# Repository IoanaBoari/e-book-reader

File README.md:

### OpenBook - Project

## Block Diagram

---
## Bill Of Materials (BOM)
| Component                   | Source                                                                                                                                                                      | Datasheet                                               |
|-----------------------------|-----------------------------------------------------------------------------------------------------------------------------------------------------------------------------|---------------------------------------------------------|
| Button                      | [Mouser](https://ro.mouser.com/ProductDetail/CK/KMR221GULCLFS?qs=u2NJ%252B70r0goBXaNk7IrU0Q%3D%3D)                                                                          |[Datasheet](https://www.ckswitches.com/media/1479/kmr2.pdf)|
| Capacitor SUPERCAP          | [Mouser](https://ro.mouser.com/ProductDetail/Seiko-Semiconductors/CPH3225A?qs=3etwrb1wR%252BhUOph6lAO7eg%3D%3D)                                                             | [Datasheet](https://ro.mouser.com/datasheet/2/360/Seiko_Instruments_MicroBattery_E_20230330_2024Jan_-3561061.pdf)|
| Capacitor 100nF             | [Mouser](https://ro.mouser.com/ProductDetail/KEMET/C0402C104K4RAL?qs=pIZUS6sqCWCaMuP2QVR%2Fog%3D%3D)                                                                        | [Datasheet](https://ro.mouser.com/datasheet/2/447/KEM_C1018_X7R_SnPb_SMD-3316276.pdf)|
| Capacitor 4.7uF             | [Mouser](https://ro.mouser.com/ProductDetail/KEMET/C0402C475M9PAC7411?qs=cpo3%2FpBou2jRzZxyxJnMGg%3D%3D)                                                                    | [Datasheet](https://ro.mouser.com/datasheet/2/447/KEM_C1006_X5R_SMD-3316465.pdf)|
| Capacitor 100uF TANT        | [Mouser](https://ro.mouser.com/ProductDetail/KYOCERA-AVX/TAJW107M010RNJ?qs=Wtp%252Bf%2FAeVqIH8v1VxV%252B1Rg%3D%3D)                                                          | [Datasheet](https://ro.mouser.com/datasheet/2/40/TAJ-3165264.pdf)|
| Capacitor 4.7uF / 25V       | [Mouser](https://ro.mouser.com/ProductDetail/KYOCERA-AVX/12063C475KAZ2A?qs=%252BdQmOuGyFcG3LdbVp5waMw%3D%3D)                                                                | [Datasheet](https://ro.mouser.com/datasheet/2/40/X7RDielectric-2943470.pdf)|
| Capacitor 1uF               | [Mouser](https://ro.mouser.com/ProductDetail/KEMET/C0402C105K9PACTU?qs=UdQET6xYxVCMExqTDkuPeQ%3D%3D)                                                                        | [Datasheet](https://ro.mouser.com/datasheet/2/447/KEM_C1006_X5R_SMD-3316465.pdf)|
| Capacitor 10uF              | [Mouser](https://ro.mouser.com/ProductDetail/KEMET/C0402C106M9PACTU?qs=x4XeXhDQKnp%252Bz0lMlwMC3A%3D%3D)                                                                    | [Datasheet](https://ro.mouser.com/datasheet/2/447/KEM_C1006_X5R_SMD-3316465.pdf)|
| CHG_LED                     | [CPC](https://cpc.farnell.com/kingbright/kpg-1608zgc/led-smd-0603-grn/dp/SC20796)                                                                                           | [Datasheet](https://www.farnell.com/datasheets/2046349.pdf)|
| USBLC6-2SC6Y                | [Mouser](https://ro.mouser.com/ProductDetail/STMicroelectronics/USBLC6-2SC6Y?qs=gNDSiZmRJS%2FOgDexvXkdow%3D%3D)                                                             | [Datasheet](https://ro.mouser.com/datasheet/2/389/usblc6_2sc6y-1852505.pdf)|
| PGB1010603MR                | [Mouser](https://ro.mouser.com/ProductDetail/Littelfuse/PGB1010603MR?qs=gu7KAQ731URLg4GSnNNN7Q%3D%3D)                                                                       | [Datasheet](https://www.littelfuse.com/assetdocs/pulseguard-esd-suppressors-pgb1-datasheet?assetguid=8a337998-d54d-466b-be4e-dc5bcd1f9321)|
| SD0805S020S1R0              | [Mouser](https://ro.mouser.com/ProductDetail/KYOCERA-AVX/SD0805S020S1R0?qs=jCA%252BPfw4LHbpkAoSnwrdjw%3D%3D)                                                                | [Datasheet](https://ro.mouser.com/datasheet/2/40/schottky-3165252.pdf)|
| MBR0530                     | [Mouser](https://ro.mouser.com/ProductDetail/onsemi/MBR0530T3G?qs=3JMERSakebpEmdUS6GetdQ%3D%3D)                                                                             | [Datasheet](https://www.onsemi.com/products/discrete-power-modules/schottky-diodes-schottky-rectifiers/mbr0530t3g)|
| Solder Jumper               | [Grabcad](https://grabcad.com/library/solder-jumpers-1)                                                                                                                     | [Datasheet](https://grabcad.com/library/solder-jumpers-1)|
| Capacitor 1uF / 50V         | [Mouser](https://ro.mouser.com/ProductDetail/TDK/C1608X7R1H105K080AB?qs=sGAEpiMZZMsh%252B1woXyUXjwVqLNpRsvnQGmKhuYn4DWE%3D)                                                 | [Datasheet](https://product.tdk.com/system/files/dam/doc/product/capacitor/ceramic/mlcc/catalog/mlcc_commercial_general_en.pdf)|
| Capacitor 0.1uF / 50V       | [Farnell](https://ro.farnell.com/multicomp-pro/mcmlr50v104kx7r/ceramic-capacitor-0-1uf-50v-x7r/dp/1600875?srsltid=AfmBOop-NuqSwaWYAsNDvdMnjraBeqfj0sl8f99iLZ_KJc8xpnT4fSqT) | [Datasheet](https://www.farnell.com/datasheets/2873577.pdf?_gl=1*x28a2*_gcl_au*MTYwODAzNzc2OC4xNzQzNDM1MjM4)|
| BD5229G-TR                  | [Mouser](https://ro.mouser.com/ProductDetail/ROHM-Semiconductor/BD5229G-TR?qs=4kLU8WoGk0vvnhrrYwdszw%3D%3D)                                                                 | [Datasheet](https://fscdn.rohm.com/en/products/databook/datasheet/ic/power/voltage_detector/bd52xxg-e.pdf)|
| XC6220A331MR-G              | [Mouser](https://ro.mouser.com/ProductDetail/Torex-Semiconductor/XC6220A331MR-G?qs=AsjdqWjXhJ8ZSWznL1J0gg%3D%3D)                                                            | [Datasheet](https://ro.mouser.com/datasheet/2/760/xc6220-3371556.pdf)|
| FH34SRJ-24S-0.5SH_99_       | [Mouser](https://ro.mouser.com/ProductDetail/Hirose-Connector/FH34SRJ-24S-0.5SH99?qs=vcbW%252B4%252BSTIpKBl5ap9J8Fw%3D%3D)                                                  | [Datasheet](https://ro.mouser.com/datasheet/2/185/FH34SRJ_24S_0_5SH_99__CL0580_1255_6_99_2DDrawing_0-1615044.pdf)|
| SAMACSYS_PARTS_USB4110-GF-A | [Mouser](https://ro.mouser.com/ProductDetail/GCT/USB4110-GF-A?qs=KUoIvG%2F9IlYiZvIXQjyJeA%3D%3D)                                                                            | [Datasheet](https://ro.mouser.com/datasheet/2/837/GCT_USB4110_Product_Drawing___20k_cycles-3455479.pdf)|
| QWIIC_RIGHT_ANGLEA          | [Mouser](https://ro.mouser.com/ProductDetail/JST-Commercial/SM04B-SRSS-TBLFSN?qs=cdbOS8ANM9B3FdyA6cNU2A%3D%3D)                                                              | [Datasheet](https://ro.mouser.com/datasheet/2/564/eSR_SZ-3476820.pdf)|
| 112A-TAAR-R03_ATTEND        | [LCSC](https://www.lcsc.com/product-detail/SD-Card-Connectors_Attend-Technology-112A-TAAR-R03_C6970445.html)                                                                | [Datasheet](https://www.lcsc.com/datasheet/lcsc_datasheet_2411220717_Attend-Technology-112A-TAAR-R03_C6970445.pdf)|
| Bobina                      | [Mouser](https://ro.mouser.com/ProductDetail/Wurth-Elektronik/744043680?qs=PGXP4M47uW6VkZq%252BkzjrHA%3D%3D)                                                                | [Datasheet](https://www.we-online.com/components/products/datasheet/744043680.pdf)|
| MCP73831                    | [Mouser](https://ro.mouser.com/ProductDetail/Microchip-Technology/MCP73831-2ACI-MC?qs=hH%252BOa0VZEiBneYTVdpuVdg%3D%3D)                                                     | [Datasheet](https://ro.mouser.com/datasheet/2/268/MCP73831_Family_Data_Sheet_DS20001984H-3441711.pdf)|
| PFMF.050.1                  | [Mouser](https://ro.mouser.com/ProductDetail/Schurter/PFMF.050.2?qs=1auRipcfynCums5v1iucSA%3D%3D)                                                                           | [Datasheet](https://ro.mouser.com/datasheet/2/358/typ_PFMF-1275918.pdf)|
| DMG2305UX-7                 | [Mouser](https://ro.mouser.com/ProductDetail/Diodes-Incorporated/DMG2305UX-7?qs=L1DZKBg7t5F%2FNBHrjfxC%252Bg%3D%3D)                                                         | [Datasheet](https://www.diodes.com/assets/Datasheets/DMG2305UX.pdf)|
| SI1308EDL-T1-GE3            | [Mouser](https://ro.mouser.com/ProductDetail/Vishay-Semiconductors/SI1308EDL-T1-GE3?qs=bX1%252BNvsK%2FBramh9tgpOaEw%3D%3D)                                                  | [Datasheet](https://www.vishay.com/docs/63399/si1308edl.pdf)|
| Resistor 10K                | [DigiKey](https://www.digikey.com/en/products/detail/venkel/CR0402-10W-102JT/12332774)                                                                                      | [Datasheet](https://data.venkel.com/documents/cr-series?_gl=1*mn27ew*_ga*MTAzMTIxOTYyMS4xNzQzNzU5MjAy*_ga_JRKGBZNVM8*MTc0Mzc1OTIwMS4xLjAuMTc0Mzc1OTIwMi41OS4wLjA.)|
| Resistor 100K               | [Venkel](https://venkel.com/part/CR0402-16W-1003FT)                                                                                                                         | [Datasheet](https://data.venkel.com/documents/cr-series?_gl=1*oleae1*_ga*MTAzMTIxOTYyMS4xNzQzNzU5MjAy*_ga_JRKGBZNVM8*MTc0Mzc1OTIwMS4xLjEuMTc0Mzc1OTM0My4zNi4wLjA.)|
| Resistor 5k1                | [Venkel](https://venkel.com/part/CR0402-10W-5101FT)                                                                                                                         | [Datasheet](https://data.venkel.com/documents/cr-series?_gl=1*1e041jc*_ga*MTAzMTIxOTYyMS4xNzQzNzU5MjAy*_ga_JRKGBZNVM8*MTc0Mzc1OTIwMS4xLjEuMTc0Mzc1OTU2Ny41MS4wLjA.)|
| Resistor 2k                 | [Venkel](https://www.venkel.com/part/CR0402-16W-2002FT)                                                                                                                     | [Datasheet](https://data.venkel.com/documents/cr-series?_gl=1*1sqolfs*_ga*MTAzMTIxOTYyMS4xNzQzNzU5MjAy*_ga_JRKGBZNVM8*MTc0Mzc1OTIwMS4xLjEuMTc0Mzc1OTY2OS4zNC4wLjA.)|
| Resistor 0.47               | [Mouser](https://ro.mouser.com/ProductDetail/Vishay-Beyschlag/MCT06030C4700FP500?qs=XsZ9OvPb0dt82KlzjdcMjQ%3D%3D)                                                           | [Datasheet](https://www.vishay.com/docs/28705/mcx0x0xpro.pdf)|
| BME688                      | [Mouser](https://ro.mouser.com/ProductDetail/Bosch-Sensortec/BME688?qs=IS%252B4QmGtzzqQoVDscqwx3A%3D%3D)                                                                    | [Datasheet](https://ro.mouser.com/datasheet/2/783/bst_bme688_fl000-2307034.pdf)|
| W25Q512JVEIQ                | [Mouser](https://ro.mouser.com/ProductDetail/Winbond/W25Q512JVEIQ?qs=l7cgNqFNU1jw6svr3at6tA%3D%3D)                                                                          | [Datasheet](https://ro.mouser.com/datasheet/2/949/Winbond_W25Q512JV_Datasheet-3240039.pdf)|
| ESP32-C6-WROOM-1-N8         | [Mouser](https://ro.mouser.com/ProductDetail/Espressif-Systems/ESP32-C6-WROOM-1-N8?qs=8Wlm6%252BaMh8ST02Gmwp74cw%3D%3D)                                                     | [Datasheet](https://ro.mouser.com/datasheet/2/891/Espressif_ESP32_C6_WROOM_1__Datasheet_V0_1_PRELIMI-3239987.pdf)|
| DS3231SN#                   | [Mouser](https://ro.mouser.com/ProductDetail/Analog-Devices-Maxim-Integrated/DS3231SN?qs=1eQvB6Dk1vhUlr8%2FOrV0Fw%3D%3D)                                                    | [Datasheet](https://ro.mouser.com/datasheet/2/609/DS3231-3421123.pdf)|
| MAX17048G+T10               | [Mouser](https://ro.mouser.com/ProductDetail/Analog-Devices-Maxim-Integrated/MAX17048G%2bT10?qs=D7PJwyCwLAoGnnn8jEPRBQ%3D%3D)                                               | [Datasheet](https://ro.mouser.com/datasheet/2/609/MAX17048_MAX17049-3469099.pdf)|
| Test Pad                    | [DigiKey](https://www.digikey.com/en/products/detail/keystone-electronics/5006/255330)                                                                                      | [Datasheet](https://www.keyelco.com/userAssets/file/M65p56.pdf)|

---

# Hardware Functionality

**Power Supply & Energy Management:**
- **USB with ESD:** Provides power and protects data lines.
- **Li-Po Charging Circuit - MCP73831:** Controlled charging for the 1800 mAh battery.
- **Li-Po Battery & LDO Voltage Regulator:** Regulates voltage to 3.3V for all modules.

**Microcontroller & Interfaces:**
- **ESP32-C6:**
    - **SPI:** Connects NOR Flash memory, SD card, and e-paper display.
    - **I2C:** Connects RTC DS3231, BME688 sensor, and expansion modules.
    - **UART:** For debugging and serial communication.
    - **GPIO:** For buttons and test pads.

**Storage & Display Modules:**
- **NOR Flash Memory (SPI)** Fast storage for firmware and data.
- **SD Card (SPI)** Expands storage capacity.
- **E-Paper Display:** Low-power, precise updates, controlled via SPI.

**Additional Modules & Sensors:**
- **RTC DS3231 (I2C):** Real-time clock.
- **BME688 Sensor (I2C):** Measures temperature, humidity, pressure, and air quality.
- **Qwiic/Stemma QT Connector (I2C):** Allows expansion with additional modules.
- **Test Pads & Buttons (GPIO):** Facilitate direct control and diagnostics.

**Power Optimization:**
- **ESP32-C6 Low-Power Mode:** Reduces consumption through dynamic frequency and activity management.
- **Stable LDO:** Ensures a constant 3.3V voltage.
- **SMD Components (e.g., 0402 capacitors):** Minimize consumption through small size and improved efficiency.

---

# ESP32-C6 Pin Mapping

| Nume | GPIO        | Usage                                          | Notes                                                                                                                           |
|------|-------------|------------------------------------------------|---------------------------------------------------------------------------------------------------------------------------------|
| 3V3  | 3V3         | 3.3V Power Supply                               | Voltage source for ESP32-C6 and logic components.                                                                       |
| SCK (SPI) | IO6         | SPI Clock                               | Provides the clock signal for high-speed data transfers.                                                                           |
| MOSI (SPI) | IO7         | SPI Data Transmission                           | Sends data to NOR Flash, SD Card, and E-Paper.                                                                               |
| MISO (SPI) | IO2         | SPI Data Reception                            | Receives data from SPI devices.                                                                                          |
| FLASH_CS | IO11        | SPI Chip Select for NOR Flash                | Selects the NOR Flash memory on the SPI bus.                                                                                 |
| EPD_CS | IO10        | SPI Chip Select for E-Paper                   | Selects the e-paper display.                                                                                                    |
| SDA (I2C) | IO21        | I2C Data Line                              | Connects RTC DS3231, BME688 sensor, and Qwiic/Stemma QT connector.                                                           |
| SCL (I2C) | IO22        | I2C Clock Line                              | Synchronizes I2C communication.                                                                                                 |
| TX (UART) | TXD0/GPIO16 | UART Data Transmission                          | Used for debugging and serial communication.                                                                                   |
| RX (UART) | RXD0/GPIO17 | UART Data Reception                             | Used for debugging and serial communication.                                                                                   |
| Buton Reset | EN          | ESP32-C6 Reset                              | Pin dedicat pentru resetul sistemului.                                                                                          |
| Buton Boot | IO9         | Bootloader Entry                          | Dedicated pin to enter boot mode.                                                                                       |
| Buton Change | IO15        | Operation Mode Switch                          | Allows switching between different operating modes.                                                                               |
| EPD DC | IO5         | Data/Command for E-Paper                   | Distinguishes between command and data signals for the display.                                                                |
| EPD RST | IO23        | E-Paper Reset                               | Resets the e-paper display when needed.                                                                                   |
| EPD BUSY | IO3         | E-Paper Busy Indicator                        | Signal indicating if the display is currently busy.                                                                                   |
| INT_RTC | IO0         | RTC Interrupt Signal (DS3231)        | Triggers the microcontroller.                                                                                                     |
| 32KHZ | IO1         | 32 kHz Clock Signal                | Oscillation line for DS3231 or other modules (not directly connected to ESP).                                                        |
| SS_SD| IO4         | SPI Chip Select for SD Card               | Selects the SD card on the SPI bus.                                                                                        |
| USB_D- | IO12        | USB Differential Line (minus)                  | Connection to the USB port.                                                                                                        |
| USB_D+ | IO13        | USB Differential Line (plus)                   | Connection to the USB port.                                                                                                        |
| RTC_RST | IO18        | External RTC Reset/Signal                         | Used to reset the real-time clock.                                                                                    |
| I2C_PW | IO19        | I2C Power/Enable Line         | Turns I2C sensors on/off to save energy.                                                |
| EPD_3V3_C | IO20        | 3.3V Power Line for E-Paper         | Provides 3.3V specifically for the e-paper display, separate from main power, to ensure signal stability. |

---
## Motivation

- **SPI** (SCK, MOSI, MISO, CS lines) provides fast transfer for external memory (Flash), SD card, and e-paper display.
- **I2C** (SDA, SCL) connects sensors (RTC, BME688) and the Qwiic connector, allowing bus sharing with low power consumption.
- **UART** (TX, RX) is used for debugging.
- **Additional GPIOs** (buttons, test pads) facilitate manual control and diagnostics.

---

## Implementation Steps

- **Schematic:** Created the schematic according to the project requirements.
- **PCB Redesign:** Redesigned the PCB and placed components on the board based on the reference model.
- **Autorouting:** Performed autorouting on both top and bottom layers, using a 0.15 mm trace width for signal lines.
- **Power Net Class:** Grouped power traces into a net class, highlighted them, and manually adjusted to 0.3 mm to ensure robust power delivery.
- **Ground Planes and Via Stitching:** Added ground planes on top and bottom layers and applied via stitching near the ESP module for optimal inter-layer connectivity.
- **3D Models:** Downloaded component 3D models from [ComponentSearchEngine](https://componentsearchengine.com/), imported them into Fusion 360, and placed them on the PCB.
- **Enclosure Integration:** Inserted the PCB into the enclosure and modified it to properly fit the buttons and connectors.
- **3D Models for Battery and Display:** Created 3D models for the battery and display, connecting wires to the corresponding test pads and ensuring correct placement inside the enclosure.
- **Export:** Finally, generated Gerber files, Pick and Place (CPL), and BOM, preparing them for upload and production.

---

## Issues Encountered and Error Acceptance Decisions

- **3D Model for Button:**  
  Could not find a 3D model for the button that perfectly matched the project requirements, so I modified an existing model to fit the design.

- **SMD-Hole Board Outline Clearance Errors at USB Connector:**  
  Encountered two SMD-Hole Board Outline Clearance errors at the USB connector. These errors were accepted according to the provided guidelines.
---

## Conclusion
 I resolved the reported issues by adjusting the PCB thickness and adding 3D models for the solder jumper and test pads.
 For the test pads, I implemented a custom model.

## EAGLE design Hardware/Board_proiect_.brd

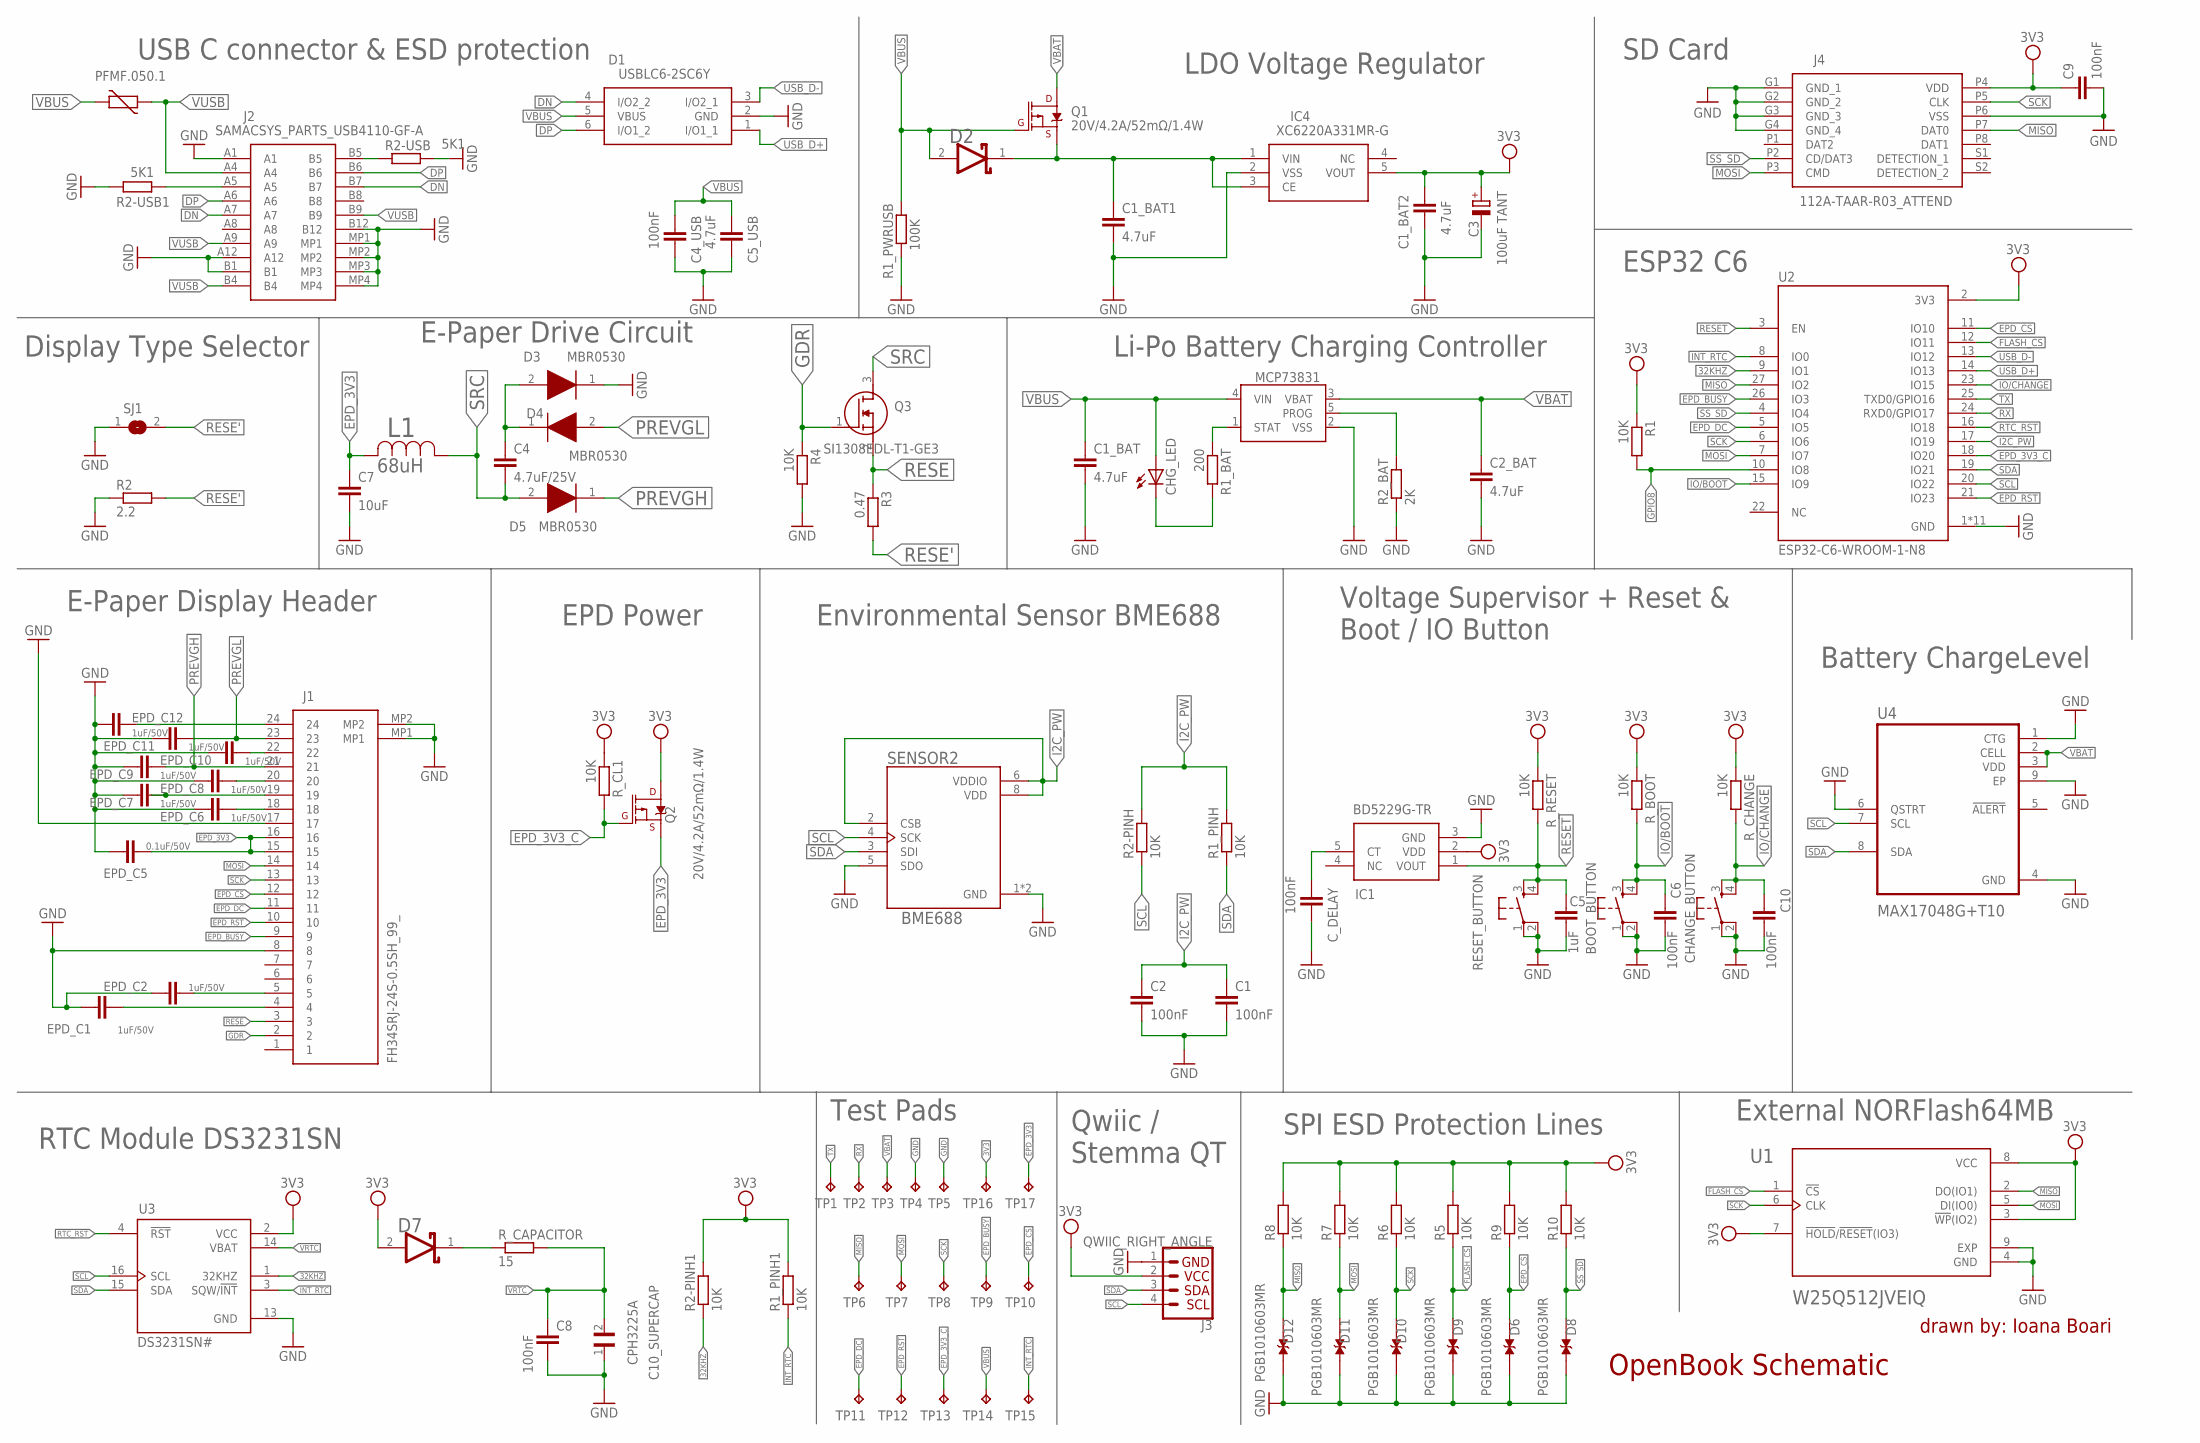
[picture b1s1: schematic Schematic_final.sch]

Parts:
BOOT_BUTTON: BUTTON_CUSYOMV1; MYBUTTON
C1, C2, C4_USB, C6, C8, C9, C10: 100nF; ESP32_WROVER_EAGLE-LTSPICE_C0402
C1_BAT, C1_BAT1, C2_BAT, C5_USB: 4.7uF; ESP32_WROVER_EAGLE-LTSPICE_C0402
C1_BAT2: 4.7uF; EAGLE-LTSPICE_C0402
C3: 100uF TANT; RCL_CT3528
C4: 4.7uF/25V; ESP32_WROVER_EAGLE-LTSPICE_C0402
C5: 1uF; ESP32_WROVER_EAGLE-LTSPICE_C0402
C7: 10uF; ESP32_WROVER_EAGLE-LTSPICE_C0402
C10_SUPERCAP: CPH3225A; CAPCP3225X100N
CHANGE_BUTTON: BUTTON_CUSYOMV1; MYBUTTON
CHG_LED: ADAFRUIT_LEDCHIP-LED0603; ADAFRUIT_CHIP-LED0603
C_DELAY: 100nF; ESP32_WROVER_EAGLE-LTSPICE_C0402
D1: USBLC6-2SC6Y; SOT95P280X145-6N
D2, D7: ESP32_WROVER_AVX---SD0805S020S1R0_AVX_SD0805S020S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; ESP32_WROVER_AVX---SD0805S020S1R0_AVX_SD0805S020S1R0_0
D3, D4, D5: MBR0530; SOD3716X135N
D6, D8, D9, D10, D11, D12: PGB1010603MR; DIOC1608X36N
EPD_C1, EPD_C2, EPD_C6, EPD_C7, EPD_C8, EPD_C9, EPD_C10, EPD_C11, EPD_C12: 1uF/50V; ESP32_WROVER_EAGLE-LTSPICE_C0402
EPD_C5: 0.1uF/50V; ESP32_WROVER_EAGLE-LTSPICE_C0402
IC1: BD5229G-TR; SOT95P280X125-5N
IC4: XC6220A331MR-G; SOT95P280X120-5N
J1: FH34SRJ-24S-0.5SH_99_; FH34SRJ24S05SH99
J2: SAMACSYS_PARTS_USB4110-GF-A; SAMACSYS_PARTS_USB4110GFA
J3: QWIIC_RIGHT_ANGLE; JST04_1MM_RA
J4: 112A-TAAR-R03_ATTEND; 112ATAARR03ATTEND
L1: 68uH; IND_4828-WE-TPC_WRE
MCP73831: MCP73831; ESP32_WROVER_SPARKFUN-IC-POWER_SOT23-5
PFMF.050.1: ESP32C6_VARISTORCN1812; ESP32C6_VARISTOR_CT/CN1812
Q1, Q2: 20V/4.2A/52mΩ/1.4W; ESP32_WROVER_SPARKFUN-DISCRETESEMI_SOT23-3
Q3: SI1308EDL-T1-GE3; SOT65P210X110-3N
R1, R1_PINH, R1_PINH1, R2-PINH, R2-PINH1, R4, R5, R6, R7, R8, R9, R10: 10K; ESP32_WROVER_EAGLE-LTSPICE_R0402
R1_BAT: 200; ESP32_WROVER_EAGLE-LTSPICE_R0402
R1_PWRUSB: 100K; ESP32_WROVER_EAGLE-LTSPICE_R0402
R2: 2.2; ESP32_WROVER_EAGLE-LTSPICE_R0402
R2-USB, R2-USB1: 5K1; ESP32_WROVER_EAGLE-LTSPICE_R0402
R2_BAT: 2K; ESP32_WROVER_EAGLE-LTSPICE_R0402
R3: 0.47; ESP32_WROVER_EAGLE-LTSPICE_R0402
RESET_BUTTON: BUTTON_CUSYOMV1; MYBUTTON
R_BOOT: 10K; ESP32_WROVER_EAGLE-LTSPICE_R0402
R_CAPACITOR: 15; ESP32_WROVER_EAGLE-LTSPICE_R0402
R_CHANGE: 10K; ESP32_WROVER_EAGLE-LTSPICE_R0402
R_CL1: 10K; ESP32_WROVER_EAGLE-LTSPICE_R0402
R_RESET: 10K; ESP32_WROVER_EAGLE-LTSPICE_R0402
SENSOR2: BME688; ESP32_WROVER_BME680_PSON80P300X300X100-8N
SJ1: SJ
TP1, TP2, TP3, TP4, TP5, TP6, TP7, TP8, TP9, TP10, TP11, TP12, TP13, TP14, TP15, TP16, TP17: TPTP20R; TP20R
U1: W25Q512JVEIQ; SON127P600X800X80-9N
U2: ESP32-C6-WROOM-1-N8; XCVR_ESP32-C6-WROOM-1-N8
U3: DS3231SN#; SOIC127P1032X265-16N
U4: MAX17048G+T10; SON50P200X200X80-9N

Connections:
3V3: C1_BAT2.1, C3.+, C9.1, D7.2 (ANODE), IC1.2 (VDD), IC4.5 (VOUT), J3.2, J4.P4 (VDD), Q2.3 (D), R1.1, R1_PINH1.2, R2-PINH1.2, R5.2, R6.2, R7.2, R8.2, R9.2, R10.2, R_BOOT.1, R_CHANGE.1, R_CL1.1, R_RESET.1, TP16.TP, U1.3 (!WP!(IO2)), U1.7 (!HOLD!/!RESET!(IO3)), U1.8 (VCC), U2.2 (3V3), U3.2 (VCC)
32KHZ: R2-PINH1.1, U2.9 (IO1), U3.1 (32KHZ)
DN: D1.4 (I/O2_2), J2.A7, J2.B7
DP: D1.6 (I/O1_2), J2.A6, J2.B6
EPD_3V3: C7.1, EPD_C5.1, J1.15, J1.16, L1.2, Q2.2 (S), TP17.TP
EPD_3V3_C: Q2.1 (G), R_CL1.2, TP13.TP, U2.18 (IO20)
EPD_BUSY: J1.9, TP9.TP, U2.26 (IO3)
EPD_CS: D6.1, J1.12, R9.1, TP10.TP, U2.11 (IO10)
EPD_DC: J1.11, TP11.TP, U2.5 (IO5)
EPD_RST: J1.10, TP12.TP, U2.21 (IO23)
FLASH_CS: D9.1, R5.1, U1.1 (!CS), U2.12 (IO11)
GDR: J1.2, Q3.1 (G), R4.1
GND: BOOT_BUTTON.1, BOOT_BUTTON.2, C1.2, C1_BAT.2, C1_BAT1.2, C1_BAT2.2, C2.2, C2_BAT.2, C3.-, C4_USB.2, C5.2, C5_USB.2, C6.2, C7.2, C8.2, C9.2, C10.2, C10_SUPERCAP.1, CHANGE_BUTTON.1, CHANGE_BUTTON.2, C_DELAY.2, D1.2 (GND), D3.1 (K), D6.2, D8.2, D9.2, D10.2, D11.2, D12.2, EPD_C1.2, EPD_C2.2, EPD_C5.2, EPD_C6.2, EPD_C7.2, EPD_C8.2, EPD_C9.2, EPD_C10.2, EPD_C11.2, EPD_C12.2, IC1.3 (GND), IC4.2 (VSS), J1.8, J1.17, J1.MP1, J1.MP2, J2.A1, J2.A12, J2.B1, J2.B12, J2.MP1, J2.MP2, J2.MP3, J2.MP4, J3.1, J4.G1 (GND_1), J4.G2 (GND_2), J4.G3 (GND_3), J4.G4 (GND_4), J4.P6 (VSS), MCP73831.2 (VSS), R1_PWRUSB.1, R2.1, R2-USB.2, R2-USB1.1, R2_BAT.1, R4.2, RESET_BUTTON.1, RESET_BUTTON.2, SENSOR2.1 (GND), SENSOR2.5 (SDO), SENSOR2.7 (GND), SJ1.1, TP4.TP, TP5.TP, U1.4 (GND), U1.9 (EXP), U2.1 (GND), U2.28 (GND), U2.29_1 (GND), U2.29_2 (GND), U2.29_3 (GND), U2.29_4 (GND), U2.29_5 (GND), U2.29_6 (GND), U2.29_7 (GND), U2.29_8 (GND), U2.29_9 (GND), U3.13 (GND), U4.1 (CTG), U4.4 (GND), U4.6 (QSTRT), U4.9 (EP)
GPIO8: R1.2, U2.10 (IO8)
I2C_PW: C1.1, C2.1, R1_PINH.2, R2-PINH.2, SENSOR2.2 (CSB), SENSOR2.6 (VDDIO), SENSOR2.8 (VDD), U2.17 (IO19)
INT_RTC: R1_PINH1.1, TP15.TP, U2.8 (IO0), U3.3 (SQW/!INT)
IO/BOOT: BOOT_BUTTON.3, BOOT_BUTTON.4, C6.1, R_BOOT.2, U2.15 (IO9)
IO/CHANGE: C10.1, CHANGE_BUTTON.3, CHANGE_BUTTON.4, R_CHANGE.2, U2.23 (IO15)
MISO: D12.1, J4.P7 (DAT0), R8.1, TP6.TP, U1.2 (DO(IO1)), U2.27 (IO2)
MOSI: D11.1, J1.14, J4.P3 (CMD), R7.1, TP7.TP, U1.5 (DI(IO0)), U2.7 (IO7)
unnamed: D7.1 (CATHODE), R_CAPACITOR.1
unnamed: EPD_C1.1, J1.4
unnamed: EPD_C2.1, J1.5
unnamed: EPD_C6.1, J1.18
unnamed: EPD_C7.1, J1.19
unnamed: EPD_C8.1, J1.20
unnamed: C_DELAY.1, IC1.5 (CT)
unnamed: EPD_C10.1, J1.22
unnamed: C4.1, D3.2 (A), D4.1 (K)
unnamed: EPD_C12.1, J1.24
unnamed: MCP73831.1 (STAT), R1_BAT.1
unnamed: CHG_LED.C, R1_BAT.2
unnamed: MCP73831.5 (PROG), R2_BAT.2
unnamed: J2.A5, R2-USB1.2
unnamed: J2.B5, R2-USB.1
unnamed: C1_BAT1.1, D2.1 (CATHODE), IC4.1 (VIN), IC4.3 (CE), Q1.2 (S)
PREVGH: D5.1 (K), EPD_C9.1, J1.21
PREVGL: D4.2 (A), EPD_C11.1, J1.23
RESE: J1.3, Q3.2 (S), R3.1
RESE': R2.2, R3.2, SJ1.2
RESET: C5.1, IC1.1 (VOUT), RESET_BUTTON.3, RESET_BUTTON.4, R_RESET.2, U2.3 (EN)
RTC_RST: U2.16 (IO18), U3.4 (!RST)
RX: TP2.TP, U2.24 (RXD0/GPIO17)
SCK: D10.1, J1.13, J4.P5 (CLK), R6.1, TP8.TP, U1.6 (CLK), U2.6 (IO6)
SCL: J3.4, R2-PINH.1, SENSOR2.4 (SCK), U2.20 (IO22), U3.16 (SCL), U4.7 (SCL)
SDA: J3.3, R1_PINH.1, SENSOR2.3 (SDI), U2.19 (IO21), U3.15 (SDA), U4.8 (SDA)
SRC: C4.2, D5.2 (A), L1.1, Q3.3 (D)
SS_SD: D8.1, J4.P2 (CD/DAT3), R10.1, U2.4 (IO4)
TX: TP1.TP, U2.25 (TXD0/GPIO16)
USB_D+: D1.1 (I/O1_1), U2.14 (IO13)
USB_D-: D1.3 (I/O2_1), U2.13 (IO12)
VBAT: C2_BAT.1, MCP73831.3 (VBAT), Q1.3 (D), TP3.TP, U4.2 (CELL), U4.3 (VDD)
VBUS: C1_BAT.1, C4_USB.1, C5_USB.1, CHG_LED.A, D1.5 (VBUS), D2.2 (ANODE), MCP73831.4 (VIN), PFMF.050.1.2, Q1.1 (G), R1_PWRUSB.2, TP14.TP
VRTC: C8.1, C10_SUPERCAP.2, R_CAPACITOR.2, U3.14 (VBAT)
VUSB: J2.A4, J2.A9, J2.B4, J2.B9, PFMF.050.1.1

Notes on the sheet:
SD Card
ESP32 C6
Battery ChargeLevel
External NORFlash64MB
SPI ESD Protection Lines
Qwiic / Stemma QT
Test Pads
RTC Module DS3231SN
E-Paper Display Header
EPD Power
Environmental Sensor BME688
Voltage Supervisor + Reset & Boot / IO Button
Display Type Selector
E-Paper Drive Circuit
Li-Po Battery Charging Controller
USB C connector & ESD protection
LDO Voltage Regulator
OpenBook Schematic
drawn by: Ioana Boari

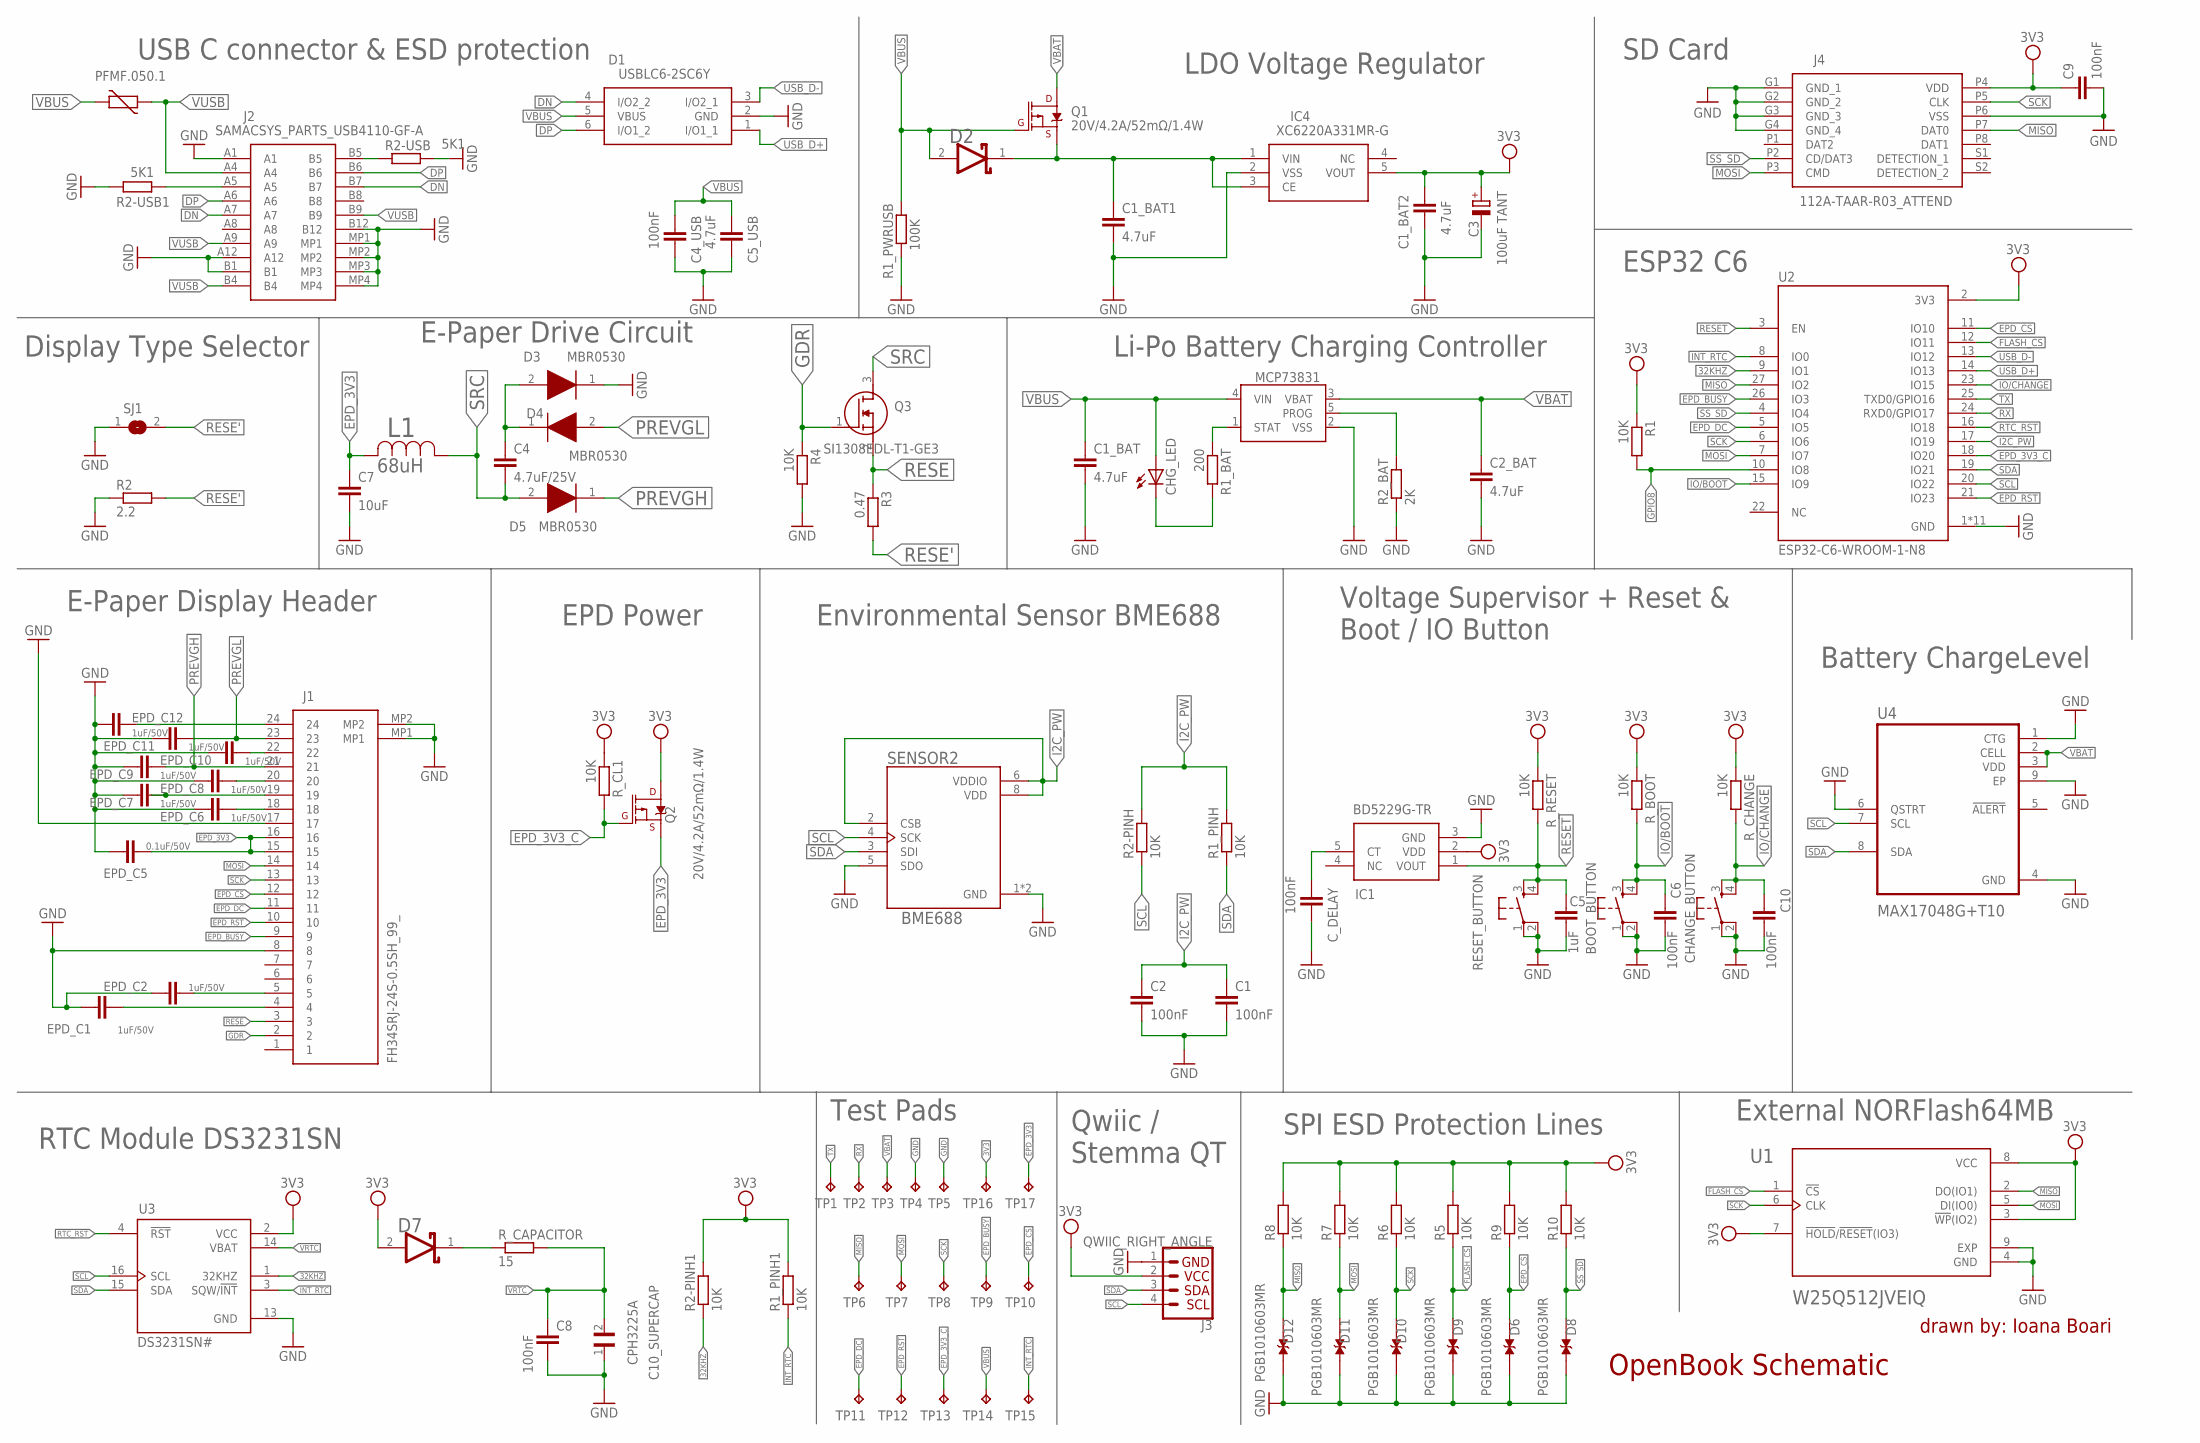
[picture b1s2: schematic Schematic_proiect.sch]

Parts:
BOOT_BUTTON: BUTTON_CUSYOMV1; MYBUTTON
C1, C2, C4_USB, C6, C8, C9, C10: 100nF; ESP32_WROVER_EAGLE-LTSPICE_C0402
C1_BAT, C1_BAT1, C2_BAT, C5_USB: 4.7uF; ESP32_WROVER_EAGLE-LTSPICE_C0402
C1_BAT2: 4.7uF; EAGLE-LTSPICE_C0402
C3: 100uF TANT; RCL_CT3528
C4: 4.7uF/25V; ESP32_WROVER_EAGLE-LTSPICE_C0402
C5: 1uF; ESP32_WROVER_EAGLE-LTSPICE_C0402
C7: 10uF; ESP32_WROVER_EAGLE-LTSPICE_C0402
C10_SUPERCAP: CPH3225A; CAPCP3225X100N
CHANGE_BUTTON: BUTTON_CUSYOMV1; MYBUTTON
CHG_LED: ADAFRUIT_LEDCHIP-LED0603; ADAFRUIT_CHIP-LED0603
C_DELAY: 100nF; ESP32_WROVER_EAGLE-LTSPICE_C0402
D1: USBLC6-2SC6Y; SOT95P280X145-6N
D2, D7: ESP32_WROVER_AVX---SD0805S020S1R0_AVX_SD0805S020S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; ESP32_WROVER_AVX---SD0805S020S1R0_AVX_SD0805S020S1R0_0
D3, D4, D5: MBR0530; SOD3716X135N
D6, D8, D9, D10, D11, D12: PGB1010603MR; DIOC1608X36N
EPD_C1, EPD_C2, EPD_C6, EPD_C7, EPD_C8, EPD_C9, EPD_C10, EPD_C11, EPD_C12: 1uF/50V; ESP32_WROVER_EAGLE-LTSPICE_C0402
EPD_C5: 0.1uF/50V; ESP32_WROVER_EAGLE-LTSPICE_C0402
IC1: BD5229G-TR; SOT95P280X125-5N
IC4: XC6220A331MR-G; SOT95P280X120-5N
J1: FH34SRJ-24S-0.5SH_99_; FH34SRJ24S05SH99
J2: SAMACSYS_PARTS_USB4110-GF-A; SAMACSYS_PARTS_USB4110GFA
J3: QWIIC_RIGHT_ANGLE; JST04_1MM_RA
J4: 112A-TAAR-R03_ATTEND; 112ATAARR03ATTEND
L1: 68uH; IND_4828-WE-TPC_WRE
MCP73831: MCP73831; ESP32_WROVER_SPARKFUN-IC-POWER_SOT23-5
PFMF.050.1: ESP32C6_VARISTORCN1812; ESP32C6_VARISTOR_CT/CN1812
Q1, Q2: 20V/4.2A/52mΩ/1.4W; ESP32_WROVER_SPARKFUN-DISCRETESEMI_SOT23-3
Q3: SI1308EDL-T1-GE3; SOT65P210X110-3N
R1, R1_PINH, R1_PINH1, R2-PINH, R2-PINH1, R4, R5, R6, R7, R8, R9, R10: 10K; ESP32_WROVER_EAGLE-LTSPICE_R0402
R1_BAT: 200; ESP32_WROVER_EAGLE-LTSPICE_R0402
R1_PWRUSB: 100K; ESP32_WROVER_EAGLE-LTSPICE_R0402
R2: 2.2; ESP32_WROVER_EAGLE-LTSPICE_R0402
R2-USB, R2-USB1: 5K1; ESP32_WROVER_EAGLE-LTSPICE_R0402
R2_BAT: 2K; ESP32_WROVER_EAGLE-LTSPICE_R0402
R3: 0.47; ESP32_WROVER_EAGLE-LTSPICE_R0402
RESET_BUTTON: BUTTON_CUSYOMV1; MYBUTTON
R_BOOT: 10K; ESP32_WROVER_EAGLE-LTSPICE_R0402
R_CAPACITOR: 15; ESP32_WROVER_EAGLE-LTSPICE_R0402
R_CHANGE: 10K; ESP32_WROVER_EAGLE-LTSPICE_R0402
R_CL1: 10K; ESP32_WROVER_EAGLE-LTSPICE_R0402
R_RESET: 10K; ESP32_WROVER_EAGLE-LTSPICE_R0402
SENSOR2: BME688; ESP32_WROVER_BME680_PSON80P300X300X100-8N
SJ1: SJ
TP1, TP2, TP3, TP4, TP5, TP6, TP7, TP8, TP9, TP10, TP11, TP12, TP13, TP14, TP15, TP16, TP17: TPTP20R; TP20R
U1: W25Q512JVEIQ; SON127P600X800X80-9N
U2: ESP32-C6-WROOM-1-N8; XCVR_ESP32-C6-WROOM-1-N8
U3: DS3231SN#; SOIC127P1032X265-16N
U4: MAX17048G+T10; SON50P200X200X80-9N

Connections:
3V3: C1_BAT2.1, C3.+, C9.1, D7.2 (ANODE), IC1.2 (VDD), IC4.5 (VOUT), J3.2, J4.P4 (VDD), Q2.3 (D), R1.1, R1_PINH1.2, R2-PINH1.2, R5.2, R6.2, R7.2, R8.2, R9.2, R10.2, R_BOOT.1, R_CHANGE.1, R_CL1.1, R_RESET.1, TP16.TP, U1.3 (!WP!(IO2)), U1.7 (!HOLD!/!RESET!(IO3)), U1.8 (VCC), U2.2 (3V3), U3.2 (VCC)
32KHZ: R2-PINH1.1, U2.9 (IO1), U3.1 (32KHZ)
DN: D1.4 (I/O2_2), J2.A7, J2.B7
DP: D1.6 (I/O1_2), J2.A6, J2.B6
EPD_3V3: C7.1, EPD_C5.1, J1.15, J1.16, L1.2, Q2.2 (S), TP17.TP
EPD_3V3_C: Q2.1 (G), R_CL1.2, TP13.TP, U2.18 (IO20)
EPD_BUSY: J1.9, TP9.TP, U2.26 (IO3)
EPD_CS: D6.1, J1.12, R9.1, TP10.TP, U2.11 (IO10)
EPD_DC: J1.11, TP11.TP, U2.5 (IO5)
EPD_RST: J1.10, TP12.TP, U2.21 (IO23)
FLASH_CS: D9.1, R5.1, U1.1 (!CS), U2.12 (IO11)
GDR: J1.2, Q3.1 (G), R4.1
GND: BOOT_BUTTON.1, BOOT_BUTTON.2, C1.2, C1_BAT.2, C1_BAT1.2, C1_BAT2.2, C2.2, C2_BAT.2, C3.-, C4_USB.2, C5.2, C5_USB.2, C6.2, C7.2, C8.2, C9.2, C10.2, C10_SUPERCAP.1, CHANGE_BUTTON.1, CHANGE_BUTTON.2, C_DELAY.2, D1.2 (GND), D3.1 (K), D6.2, D8.2, D9.2, D10.2, D11.2, D12.2, EPD_C1.2, EPD_C2.2, EPD_C5.2, EPD_C6.2, EPD_C7.2, EPD_C8.2, EPD_C9.2, EPD_C10.2, EPD_C11.2, EPD_C12.2, IC1.3 (GND), IC4.2 (VSS), J1.8, J1.17, J1.MP1, J1.MP2, J2.A1, J2.A12, J2.B1, J2.B12, J2.MP1, J2.MP2, J2.MP3, J2.MP4, J3.1, J4.G1 (GND_1), J4.G2 (GND_2), J4.G3 (GND_3), J4.G4 (GND_4), J4.P6 (VSS), MCP73831.2 (VSS), R1_PWRUSB.1, R2.1, R2-USB.2, R2-USB1.1, R2_BAT.1, R4.2, RESET_BUTTON.1, RESET_BUTTON.2, SENSOR2.1 (GND), SENSOR2.5 (SDO), SENSOR2.7 (GND), SJ1.1, TP4.TP, TP5.TP, U1.4 (GND), U1.9 (EXP), U2.1 (GND), U2.28 (GND), U2.29_1 (GND), U2.29_2 (GND), U2.29_3 (GND), U2.29_4 (GND), U2.29_5 (GND), U2.29_6 (GND), U2.29_7 (GND), U2.29_8 (GND), U2.29_9 (GND), U3.13 (GND), U4.1 (CTG), U4.4 (GND), U4.6 (QSTRT), U4.9 (EP)
GPIO8: R1.2, U2.10 (IO8)
I2C_PW: C1.1, C2.1, R1_PINH.2, R2-PINH.2, SENSOR2.2 (CSB), SENSOR2.6 (VDDIO), SENSOR2.8 (VDD), U2.17 (IO19)
INT_RTC: R1_PINH1.1, TP15.TP, U2.8 (IO0), U3.3 (SQW/!INT)
IO/BOOT: BOOT_BUTTON.3, BOOT_BUTTON.4, C6.1, R_BOOT.2, U2.15 (IO9)
IO/CHANGE: C10.1, CHANGE_BUTTON.3, CHANGE_BUTTON.4, R_CHANGE.2, U2.23 (IO15)
MISO: D12.1, J4.P7 (DAT0), R8.1, TP6.TP, U1.2 (DO(IO1)), U2.27 (IO2)
MOSI: D11.1, J1.14, J4.P3 (CMD), R7.1, TP7.TP, U1.5 (DI(IO0)), U2.7 (IO7)
unnamed: D7.1 (CATHODE), R_CAPACITOR.1
unnamed: EPD_C1.1, J1.4
unnamed: EPD_C2.1, J1.5
unnamed: EPD_C6.1, J1.18
unnamed: EPD_C7.1, J1.19
unnamed: EPD_C8.1, J1.20
unnamed: C_DELAY.1, IC1.5 (CT)
unnamed: EPD_C10.1, J1.22
unnamed: C4.1, D3.2 (A), D4.1 (K)
unnamed: EPD_C12.1, J1.24
unnamed: MCP73831.1 (STAT), R1_BAT.1
unnamed: CHG_LED.C, R1_BAT.2
unnamed: MCP73831.5 (PROG), R2_BAT.2
unnamed: J2.A5, R2-USB1.2
unnamed: J2.B5, R2-USB.1
unnamed: C1_BAT1.1, D2.1 (CATHODE), IC4.1 (VIN), IC4.3 (CE), Q1.2 (S)
PREVGH: D5.1 (K), EPD_C9.1, J1.21
PREVGL: D4.2 (A), EPD_C11.1, J1.23
RESE: J1.3, Q3.2 (S), R3.1
RESE': R2.2, R3.2, SJ1.2
RESET: C5.1, IC1.1 (VOUT), RESET_BUTTON.3, RESET_BUTTON.4, R_RESET.2, U2.3 (EN)
RTC_RST: U2.16 (IO18), U3.4 (!RST)
RX: TP2.TP, U2.24 (RXD0/GPIO17)
SCK: D10.1, J1.13, J4.P5 (CLK), R6.1, TP8.TP, U1.6 (CLK), U2.6 (IO6)
SCL: J3.4, R2-PINH.1, SENSOR2.4 (SCK), U2.20 (IO22), U3.16 (SCL), U4.7 (SCL)
SDA: J3.3, R1_PINH.1, SENSOR2.3 (SDI), U2.19 (IO21), U3.15 (SDA), U4.8 (SDA)
SRC: C4.2, D5.2 (A), L1.1, Q3.3 (D)
SS_SD: D8.1, J4.P2 (CD/DAT3), R10.1, U2.4 (IO4)
TX: TP1.TP, U2.25 (TXD0/GPIO16)
USB_D+: D1.1 (I/O1_1), U2.14 (IO13)
USB_D-: D1.3 (I/O2_1), U2.13 (IO12)
VBAT: C2_BAT.1, MCP73831.3 (VBAT), Q1.3 (D), TP3.TP, U4.2 (CELL), U4.3 (VDD)
VBUS: C1_BAT.1, C4_USB.1, C5_USB.1, CHG_LED.A, D1.5 (VBUS), D2.2 (ANODE), MCP73831.4 (VIN), PFMF.050.1.2, Q1.1 (G), R1_PWRUSB.2, TP14.TP
VRTC: C8.1, C10_SUPERCAP.2, R_CAPACITOR.2, U3.14 (VBAT)
VUSB: J2.A4, J2.A9, J2.B4, J2.B9, PFMF.050.1.1

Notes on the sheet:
SD Card
ESP32 C6
Battery ChargeLevel
External NORFlash64MB
SPI ESD Protection Lines
Qwiic / Stemma QT
Test Pads
RTC Module DS3231SN
E-Paper Display Header
EPD Power
Environmental Sensor BME688
Voltage Supervisor + Reset & Boot / IO Button
Display Type Selector
E-Paper Drive Circuit
Li-Po Battery Charging Controller
USB C connector & ESD protection
LDO Voltage Regulator
OpenBook Schematic
drawn by: Ioana Boari

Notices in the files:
parts and their libraries:
COPYRIGHT: Copyright (C) 2024 Ultra Librarian. All rights reserved.
